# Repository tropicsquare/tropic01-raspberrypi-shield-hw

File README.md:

# TROPIC01 Raspberry Pi Shield

This repository contains the design files for the TROPIC01 development shield, designed for the Raspberry Pi form factor. Each folder corresponds to a specific PCB revision.

### About TROPIC01

For more information about the TROPIC01 secure element, please see the official documentation:

*   [TROPIC01 Datasheet](https://github.com/tropicsquare/tropic01/tree/main/doc/datasheet)
*   [TROPIC01 Website](https://www.tropicsquare.com/tropic01)

# Raspberrypi Shield's Versions

Following table shows all versions of distributed shields.

| hw revision    | Picture                                                                                                            |
|----------------|----------------------------------------|
| 1501           |  [Top](./TS1501_design/img/top.png)    |

# Getting Started

To interact with the TROPIC01 chip on Linux-based systems like Raspberry Pi OS and Ubuntu, we provide the [`libtropic-linux`](https://github.com/tropicsquare/libtropic-linux) repository, containing integration examples of our platform-independent SDK, [`libtropic`](https://github.com/tropicsquare/libtropic).

 > [!IMPORTANT]
 > Before you start with various examples, we strongly recommend to do two things first:
 > * Read CHIP ID and TROPIC01's firmware versions and **save printed output for future reference**
 > * Update TROPIC01's both internal firmware to latest version.

In [`libtropic-linux`](https://github.com/tropicsquare/libtropic-linux) repository, you can find specifice instruction for both operations based on hardware you use.

### Command line utility

Once you saved results of `show_chip_id_and_fw_ver` example (for future reference) and after your chip is updated with `fw_update` example, you can test our comand line application. Check out [`lt-util`](https://github.com/tropicsquare/libtropic-util) repository, you can find there specifice instruction based on hardware you use.

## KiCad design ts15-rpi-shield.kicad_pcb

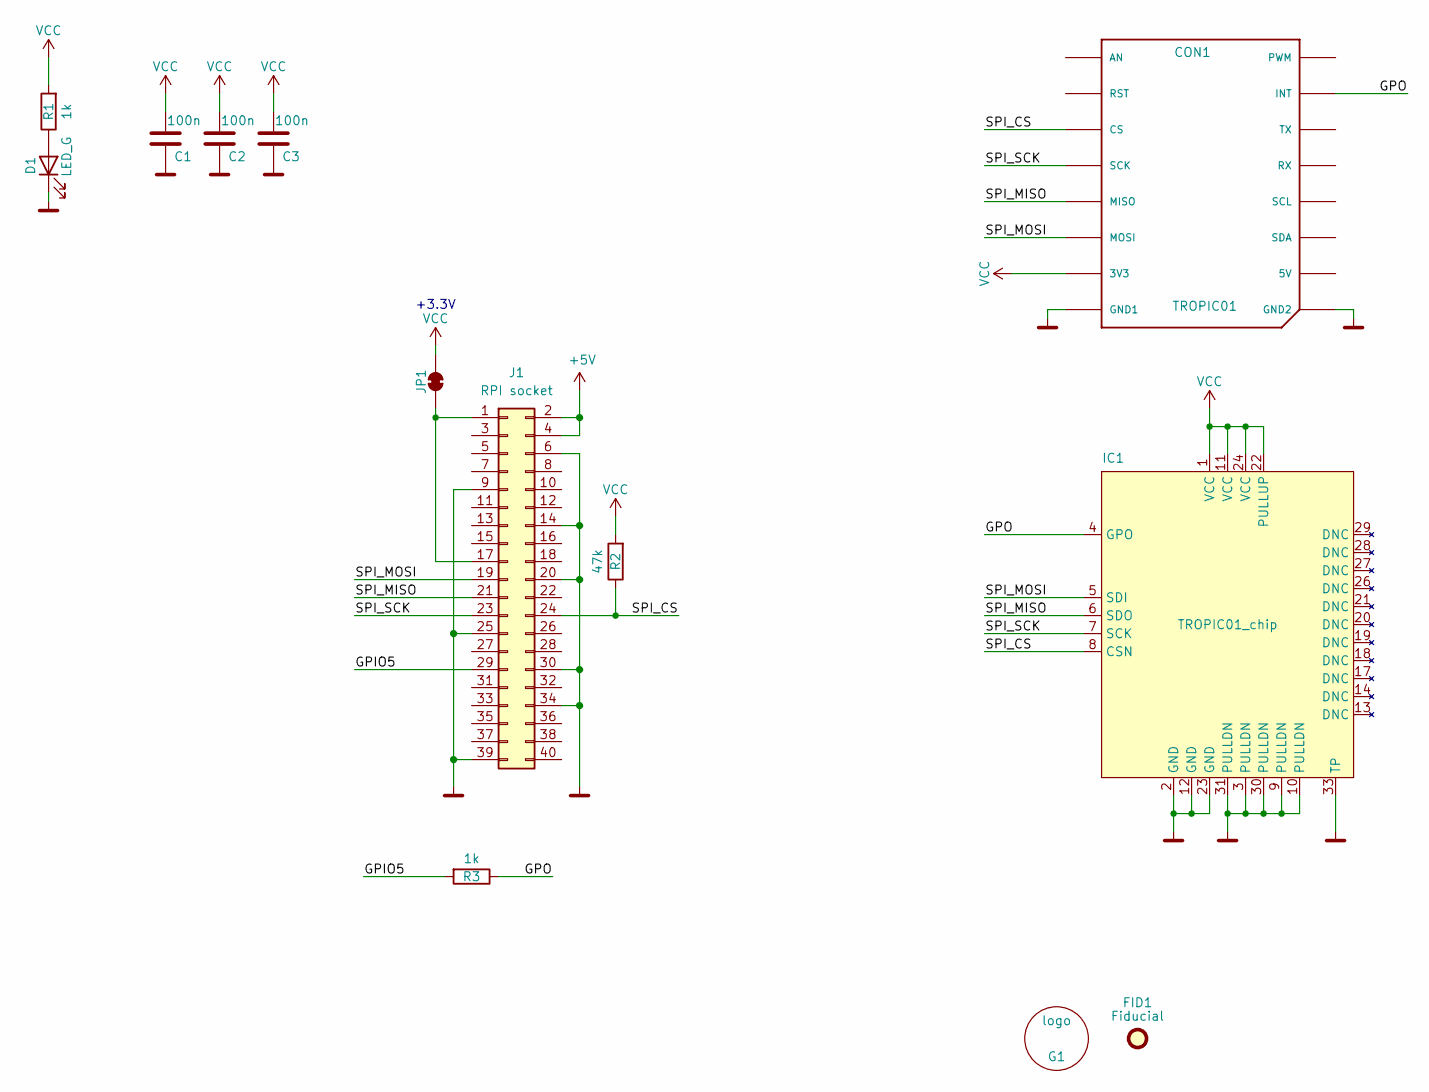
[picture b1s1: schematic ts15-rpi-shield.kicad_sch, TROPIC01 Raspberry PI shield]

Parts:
C1, C2, C3: 100n; C_0805_2012Metric_Pad1.18x1.45mm_HandSolder
CON1: TROPIC01; TROPIC01_mikrobus
D1: LED_G; LED_0805_2012Metric
FID1: Fiducial; Fiducial_0.5mm_Mask1mm
G1: logo; tropicsquare_logo
IC1: TROPIC01_chip; QFN-32-1EP_4x4mm_P0.4mm_EP2.65x2.65mm
J1: RPI socket; RPI_Hat_B+
JP1: SolderJumper_2_Bridged; SolderJumper-2_P1.3mm_Bridged
R1, R3: 1k; R_0805_2012Metric_Pad1.20x1.40mm_HandSolder
R2: 47k; R_0805_2012Metric_Pad1.20x1.40mm_HandSolder

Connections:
+5V: J1.2, J1.4
/GPIO5: J1.29, R3.2
/GPO: CON1.P15 (INT), IC1.4 (GPO), R3.1
/SPI_CS: CON1.P3 (CS), IC1.8 (CSN), J1.24, R2.1
/SPI_MISO: CON1.P5 (MISO), IC1.6 (SDO), J1.21
/SPI_MOSI: CON1.P6 (MOSI), IC1.5 (SDI), J1.19
/SPI_SCK: CON1.P4 (SCK), IC1.7 (SCK), J1.23
GND: C1.1, C2.1, C3.1, CON1.P8 (GND1), CON1.P9 (GND2), D1.1 (K), IC1.2 (GND), IC1.3 (PULLDN), IC1.9 (PULLDN), IC1.10 (PULLDN), IC1.12 (GND), IC1.23 (GND), IC1.30 (PULLDN), IC1.31 (PULLDN), IC1.33 (TP), J1.6, J1.9, J1.14, J1.20, J1.25, J1.30, J1.34, J1.39
unnamed: D1.2 (A), R1.1
unnamed: J1.1, J1.17, JP1.1 (A)
VCC: C1.2, C2.2, C3.2, CON1.P7 (3V3), IC1.1 (VCC), IC1.11 (VCC), IC1.22 (PULLUP), IC1.24 (VCC), JP1.2 (B), R1.2, R2.2

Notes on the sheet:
+3.3V

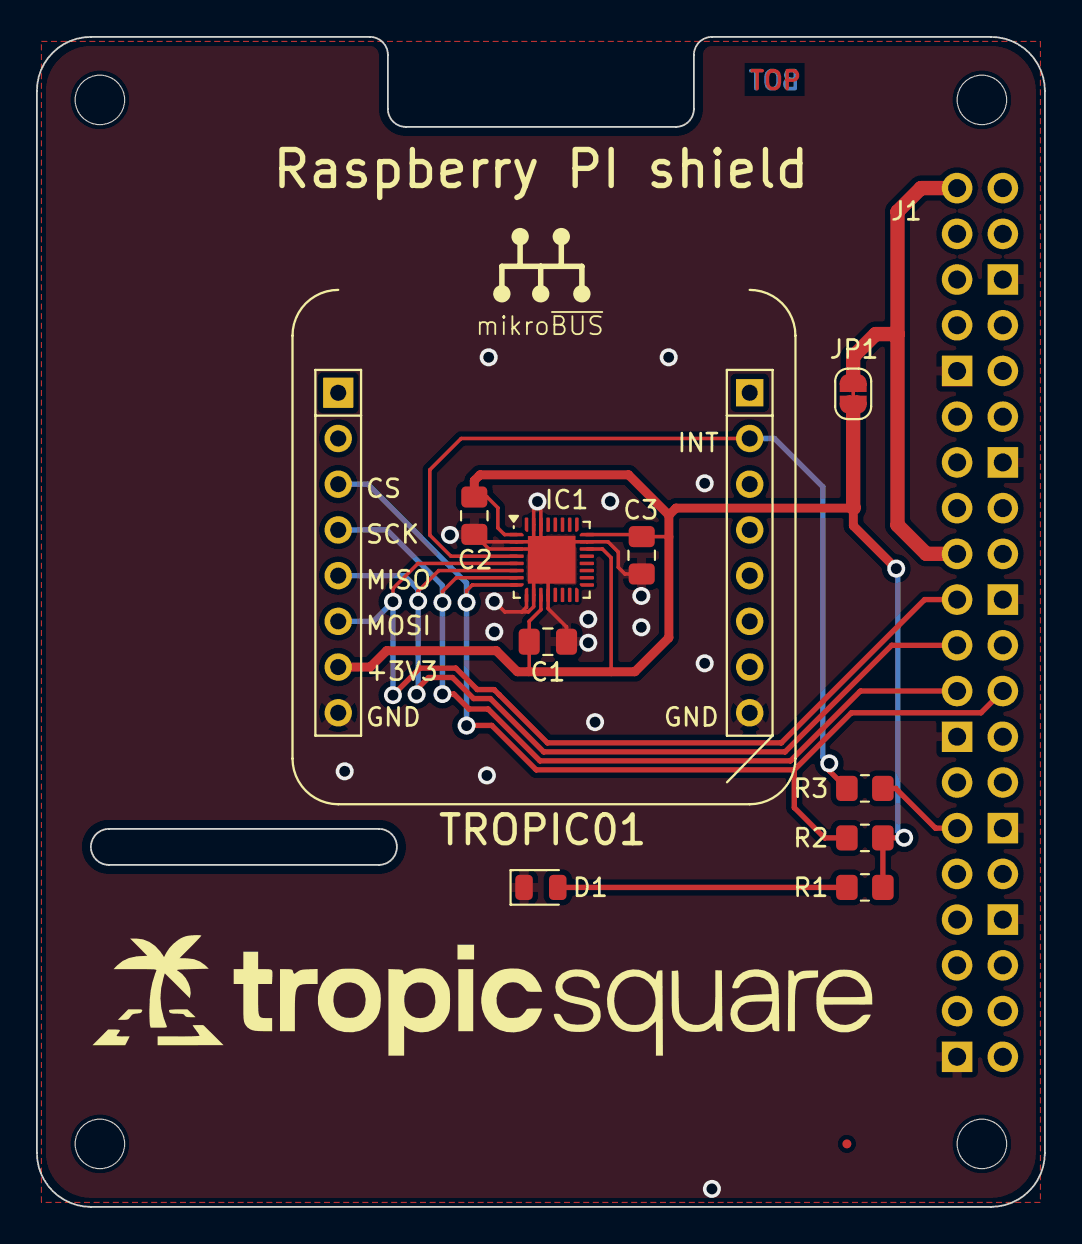
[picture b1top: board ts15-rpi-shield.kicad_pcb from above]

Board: 2 copper layers, 56.0 x 65.0 mm, 13 parts (0 on the bottom side), 11 nets.

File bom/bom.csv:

"Reference","Value","Footprint","Qty","DNP","OC_MOUSER"
"C1,C2,C3","100n","Capacitor_SMD:C_0805_2012Metric_Pad1.18x1.45mm_HandSolder","3","","187-CL21B104KBFNNNE"
"CON1","TROPIC01","ts_mikrobus:TROPIC01_mikrobus","1","","932-MIKROE-4247"
"D1","LED_G","LED_SMD:LED_0805_2012Metric","1","","710-150080GS75000"
"IC1","TROPIC01_chip","tropic01_chip:QFN-32-1EP_4x4mm_P0.4mm_EP2.65x2.65mm","1","",""
"J1","RPI socket","shields:RPI_Hat_B+","1","","474-PRT-16763"
"R1,R3","1k","Resistor_SMD:R_0805_2012Metric_Pad1.20x1.40mm_HandSolder","2","","603-RC0805JR-071KL"
"R2","47k","Resistor_SMD:R_0805_2012Metric_Pad1.20x1.40mm_HandSolder","1","","603-RC0805JR-0747KL"

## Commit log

2025-02-19 project: Add basic files (schematic and PCB)
2025-02-19 project: Add fabrication gerber data and some tuning
2025-05-13 fix: Better part number for RPI shield connector (stackable)
2025-06-13 doc: Extend README
2025-08-28 doc, ref (./) : Readme and repository refactor
2025-12-10 fix: Update BOM to fix wrong assembly of MIKROE socket
